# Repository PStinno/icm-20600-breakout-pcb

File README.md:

# icm-20600-breakout-pcb
Breakout board for the ICM 20600 3-axis Accelerometer and Gyroscope.

This board allows for use of the ICM 20600 3-axis Accelerometer + 3-axis Gyroscope, from TDK InvenSense, with both 3.3 and 5V microcontroller development boards. The sensor is powered by an onboard, low-dropout 1.8V regulator and level shifting circuitry is included for the SDA and SCL lines. As well as a 0.1 inch header for use on a bread-board, two JST-SH connectors are provided which are compatible with the Sparkfun Qwiic and Adafruit StemmaQT standards. These connectors allow for chaining of the board with other compatible boards.

Also included in the repository is a basic example for reading the sensor and configuring its measurement ranges from an Arduino Uno or similar microcontroller board. This prints readings to the USB serial port and a processing sketch is included that visualises data from two of the accelerometer axis (see above image).

[![CC BY-SA 4.0][cc-by-sa-image]][cc-by-sa]

[cc-by-sa]: http://creativecommons.org/licenses/by-sa/4.0/
[cc-by-sa-image]: https://licensebuttons.net/l/by-sa/4.0/88x31.png
[cc-by-sa-shield]: https://img.shields.io/badge/License-CC%20BY--SA%204.0-lightgrey.svg

This work is licensed under a [Creative Commons Attribution-ShareAlike 4.0 International License][cc-by-sa].

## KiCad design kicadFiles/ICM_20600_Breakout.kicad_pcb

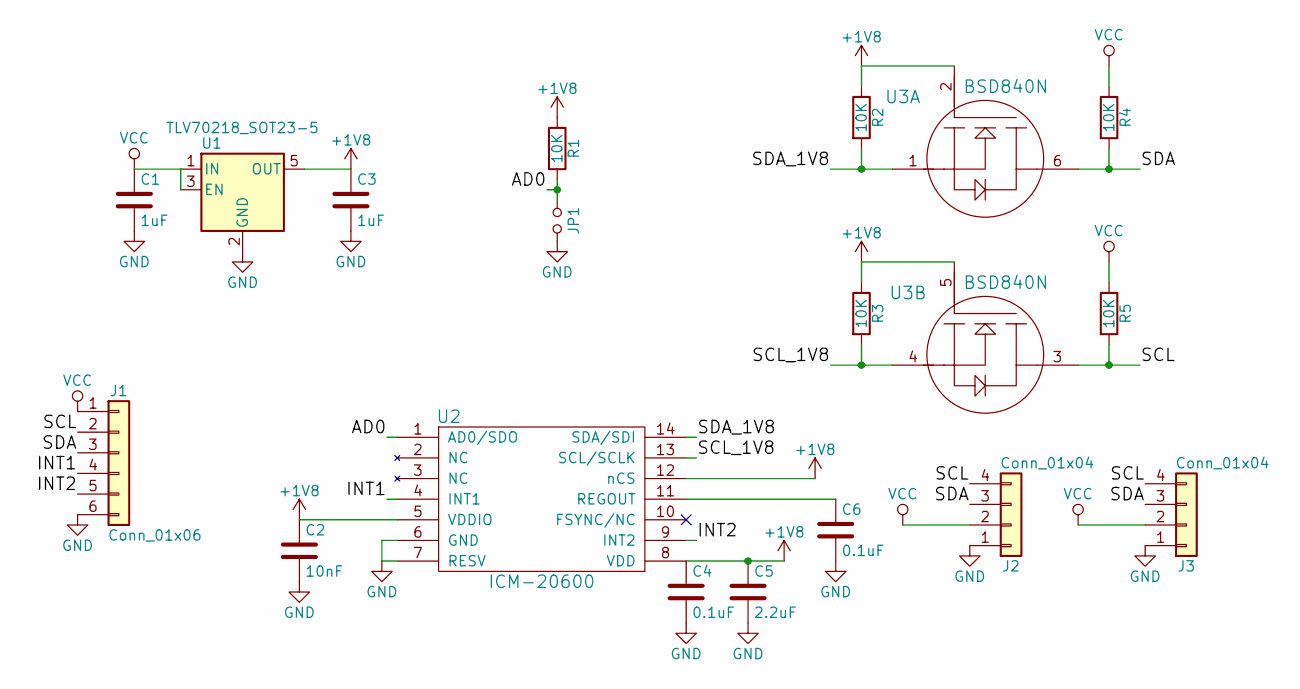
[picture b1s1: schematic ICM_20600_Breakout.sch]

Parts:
C1, C3: 1uF; C_0603
C2: 10nF; C_0603
C4, C6: 0.1uF; C_0603
C5: 2.2uF; C_0603
J1: Conn_01x06; Pin_Header_Straight_1x06_Pitch2.54mm
J2, J3: Conn_01x04; JST_SH_SM04B-SRSS-TB_04x1.00mm_Angled
JP1: Jumper_NO_Small; GS2
R1, R2, R3, R4, R5: 10K; R_0603
U1: TLV70218_SOT23-5; SOT-23-5
U2: ICM-20600; Bosch_LGA-14_3x2.5mm_Pitch0.5mm
U3: BSD840N; SOT-363_SC-70-6

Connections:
+1V8: C2.1, C3.1, C4.1, C5.1, R1.1, R2.1, R3.1, U1.5 (OUT), U2.5 (VDDIO), U2.8 (VDD), U2.12 (nCS), U3.2, U3.5
/AD0: JP1.1, R1.2, U2.1 (AD0/SDO)
/INT1: J1.4, U2.4 (INT1)
/INT2: J1.5, U2.9 (INT2)
/SCL: J1.2, J2.4, J3.4, R5.2, U3.3
/SCL_1V8: R3.2, U2.13 (SCL/SCLK), U3.4
/SDA: J1.3, J2.3, J3.3, R4.2, U3.6
/SDA_1V8: R2.2, U2.14 (SDA/SDI), U3.1
GND: C1.2, C2.2, C3.2, C4.2, C5.2, C6.2, J1.6, J2.1, J3.1, JP1.2, U1.2 (GND), U2.6 (GND), U2.7 (RESV)
unnamed: C6.1, U2.11 (REGOUT)
VCC: C1.1, J1.1, J2.2, J3.2, R4.1, R5.1, U1.1 (IN), U1.3 (EN)

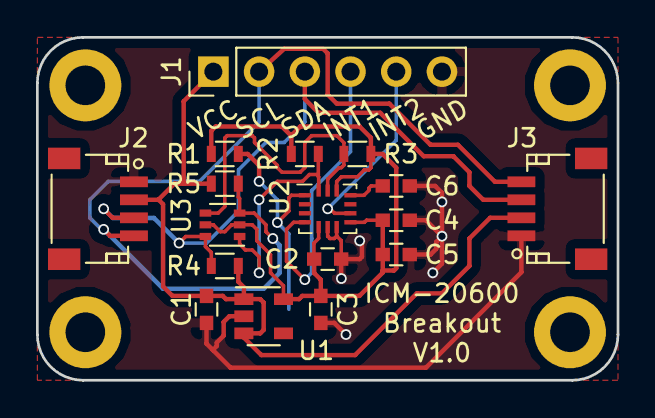
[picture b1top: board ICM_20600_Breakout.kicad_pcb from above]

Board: 2 copper layers, 32.3 x 19.1 mm, 18 parts (1 on the bottom side), 11 nets.

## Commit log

2020-03-18 Upload images of project
2020-03-18 Added Kicad design files
2020-03-18 Added Arduino and Processing code for usage example
2022-04-14 Add license to readme
2022-04-14 Added license file
